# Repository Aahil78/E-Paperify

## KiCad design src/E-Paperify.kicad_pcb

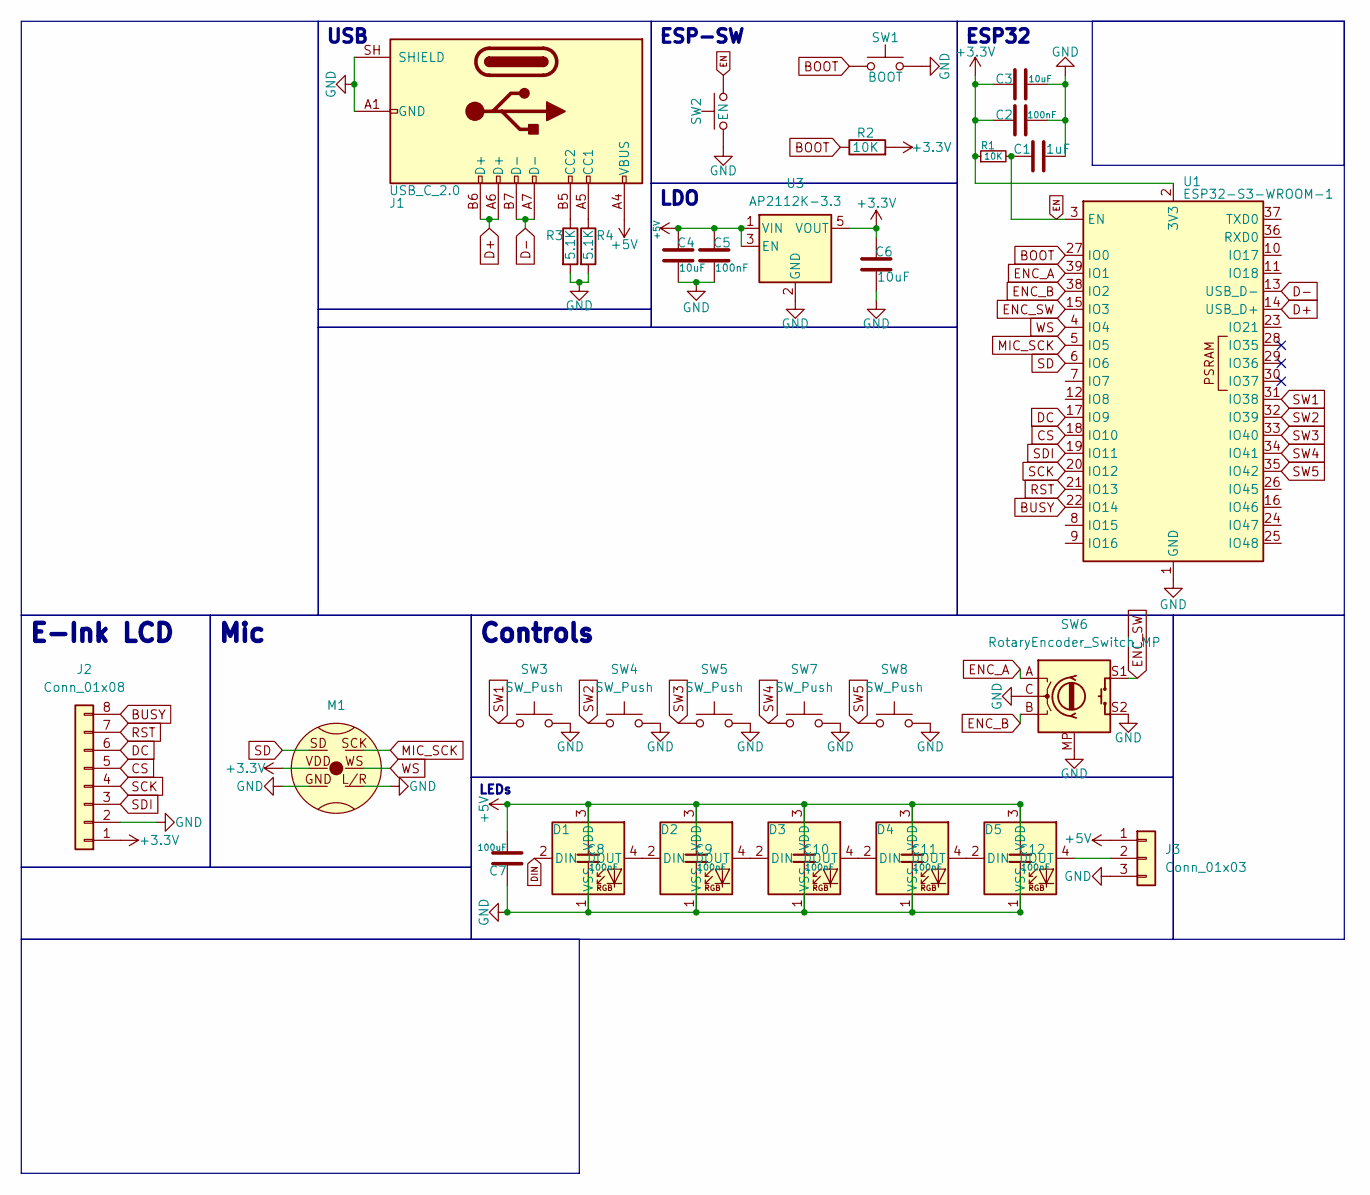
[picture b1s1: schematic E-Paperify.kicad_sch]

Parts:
C1: 1uF; C_0805_2012Metric_Pad1.18x1.45mm_HandSolder
C2, C5, C8, C9, C10, C11, C12: 100nF; C_0805_2012Metric_Pad1.18x1.45mm_HandSolder
C3, C4, C6: 10uF; C_0805_2012Metric_Pad1.18x1.45mm_HandSolder
C7: 100uF; C_0805_2012Metric_Pad1.18x1.45mm_HandSolder
D1, D2, D3, D4, D5: SK6812MINI-E; MX_SK6812MINI-E
J1: USB_C_2.0; USB_C_Receptacle_GCT_USB4110
J2: Conn_01x08; PinHeader_1x08_P2.54mm_Vertical
J3: Conn_01x03; PinHeader_1x03_P2.54mm_Vertical
M1: INMP441
R1, R2: 10K; R_0805_2012Metric_Pad1.20x1.40mm_HandSolder
R3, R4: 5.1K; R_0805_2012Metric_Pad1.20x1.40mm_HandSolder
SW1: BOOT; SW_Push_1P1T_XKB_TS-1187A
SW2: EN; SW_Push_1P1T_XKB_TS-1187A
SW3, SW4, SW5, SW7, SW8: SW_Push; SW_Hotswap_Kailh_MX_1.00u
SW6: RotaryEncoder_Switch_MP; RotaryEncoder_Alps_EC11E-Switch_Vertical_H20mm
U1: ESP32-S3-WROOM-1
U3: AP2112K-3.3; SOT-23-5

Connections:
+3.3V: C2.1, C3.1, C6.1, J2.1, M1.VDD, R1.1, R2.2, U1.2 (3V3), U3.5 (VOUT)
+5V: C4.1, C5.1, C7.2, C8.1, C9.1, C10.1, C11.1, C12.1, D1.3 (VDD), D2.3 (VDD), D3.3 (VDD), D4.3 (VDD), D5.3 (VDD), J1.A4 (VBUS), J1.A9 (VBUS), J1.B4 (VBUS), J1.B9 (VBUS), J3.1, U3.1 (VIN), U3.3 (EN)
BOOT: R2.1, SW1.1, U1.27 (IO0)
BUSY: J2.8, U1.22 (IO14)
CS: J2.5, U1.18 (IO10)
D+: J1.A6 (D+), J1.B6 (D+), U1.14 (USB_D+)
D-: J1.A7 (D-), J1.B7 (D-), U1.13 (USB_D-)
DC: J2.6, U1.17 (IO9)
DIN: D1.2 (DIN)
EN: C1.1, R1.2, SW2.2, U1.3 (EN)
ENC_A: SW6.A, U1.39 (IO1)
ENC_B: SW6.B, U1.38 (IO2)
ENC_SW: SW6.S1, U1.15 (IO3)
GND: C1.2, C2.2, C3.2, C4.2, C5.2, C6.2, C7.1, C8.2, C9.2, C10.2, C11.2, C12.2, D1.1 (VSS), D2.1 (VSS), D3.1 (VSS), D4.1 (VSS), D5.1 (VSS), J1.A1 (GND), J1.A12 (GND), J1.B1 (GND), J1.B12 (GND), J1.SH (SHIELD), J2.2, J3.3, M1.GND, M1.L/R, R3.2, R4.2, SW1.2, SW2.1, SW3.2, SW4.2, SW5.2, SW6.C, SW6.MP, SW6.S2, SW7.2, SW8.2, U1.1 (GND), U1.40 (GND), U1.41 (GND), U3.2 (GND)
MIC_SCK: M1.SCK, U1.5 (IO5)
unnamed: D1.4 (DOUT), D2.2 (DIN)
unnamed: D2.4 (DOUT), D3.2 (DIN)
unnamed: D3.4 (DOUT), D4.2 (DIN)
unnamed: D4.4 (DOUT), D5.2 (DIN)
unnamed: D5.4 (DOUT), J3.2
unnamed: J1.A5 (CC1), R4.1
unnamed: J1.B5 (CC2), R3.1
RST: J2.7, U1.21 (IO13)
SCK: J2.4, U1.20 (IO12)
SD: M1.SD, U1.6 (IO6)
SDI: J2.3, U1.19 (IO11)
SW1: SW3.1, U1.31 (IO38)
SW2: SW4.1, U1.32 (IO39)
SW3: SW5.1, U1.33 (IO40)
SW4: SW7.1, U1.34 (IO41)
SW5: SW8.1, U1.35 (IO42)
WS: M1.WS, U1.4 (IO4)

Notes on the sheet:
ESP32
LEDs
E-Ink LCD
LDO
Mic
ESP-SW
Controls
USB

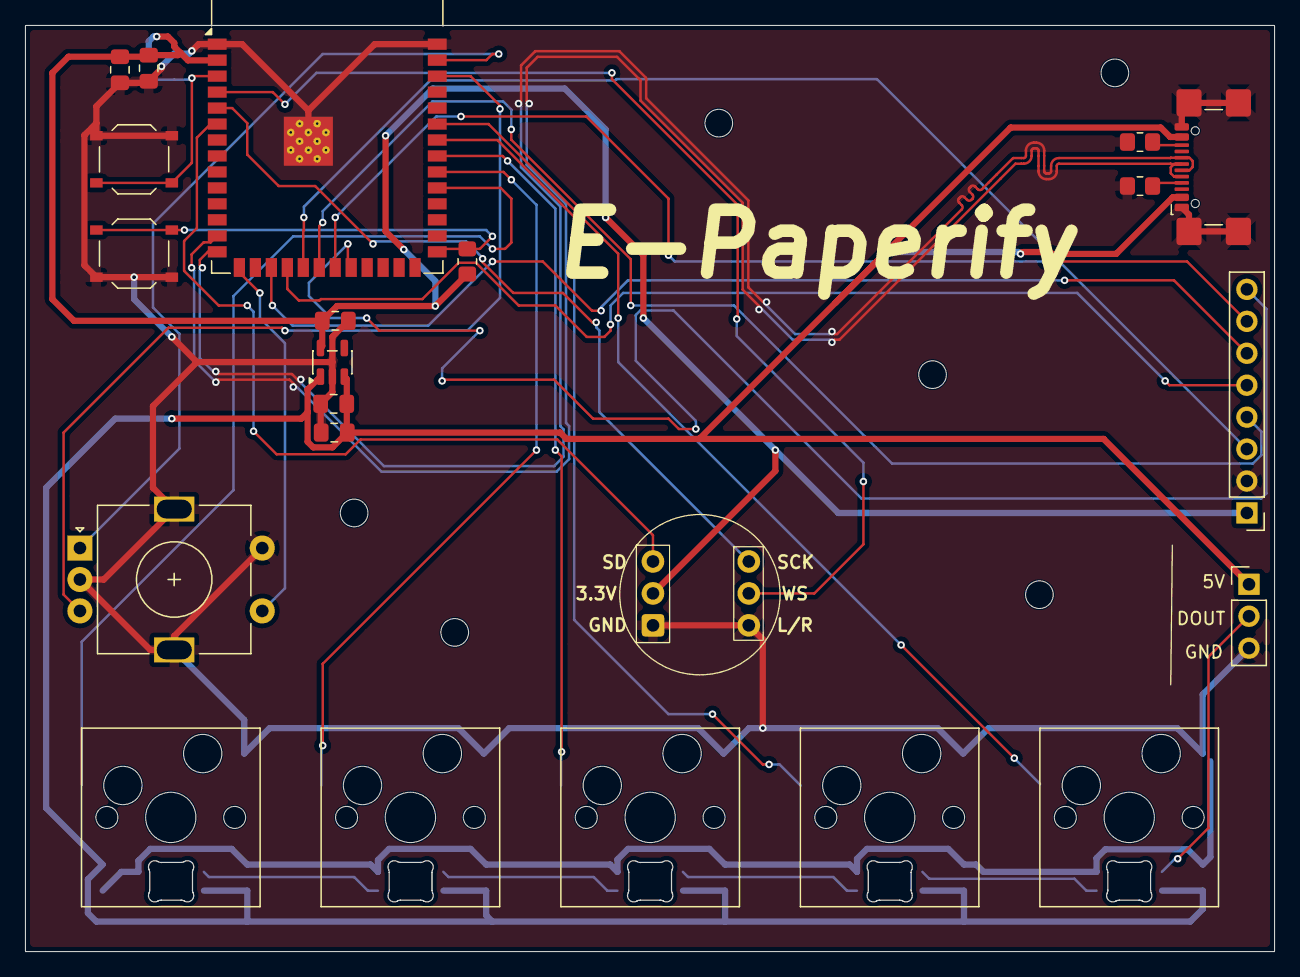
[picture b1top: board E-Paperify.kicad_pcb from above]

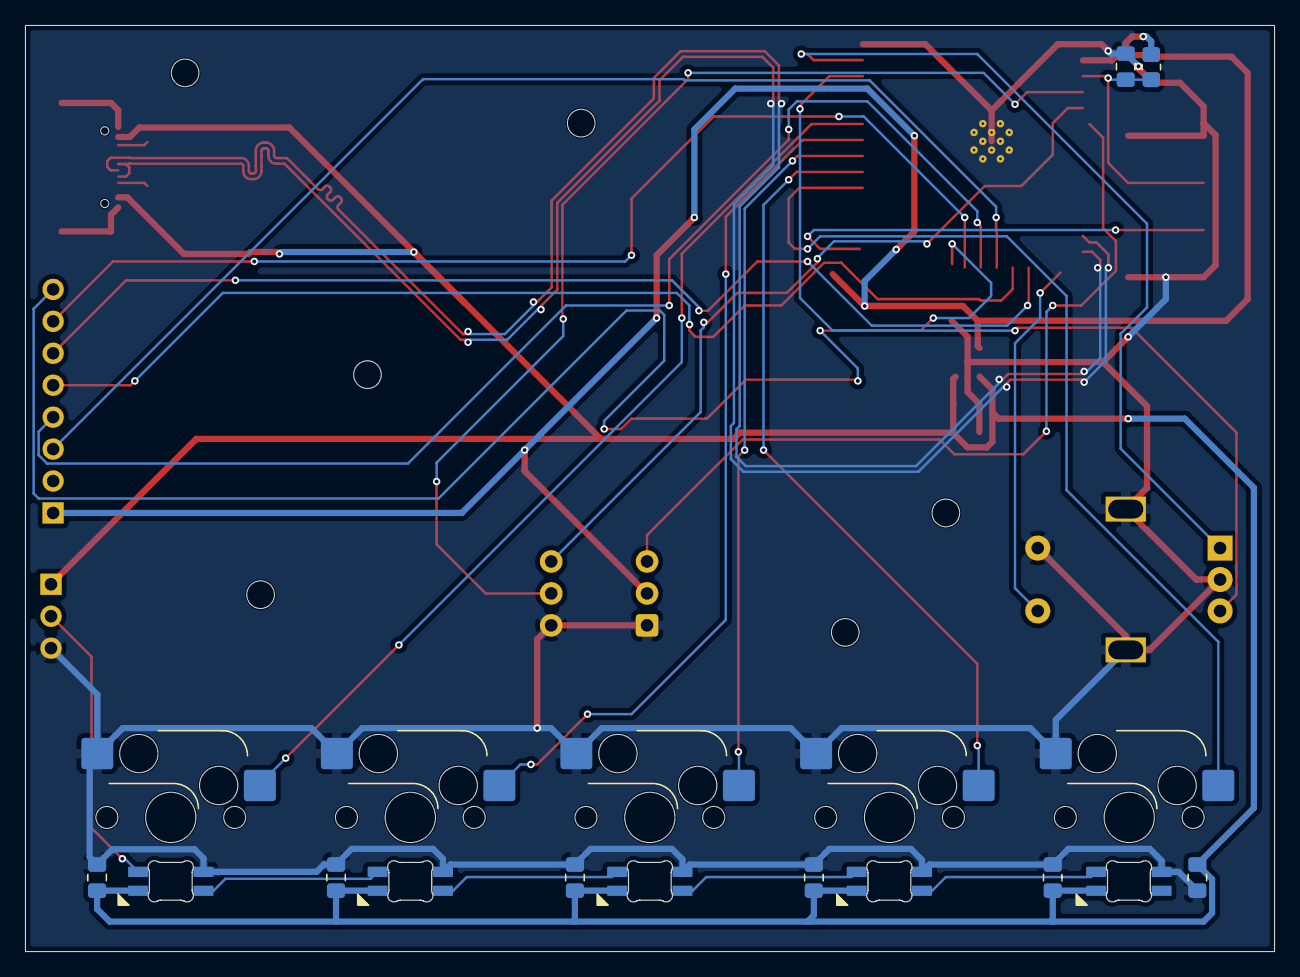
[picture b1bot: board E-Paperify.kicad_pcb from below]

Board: 2 copper layers, 99.3 x 73.7 mm, 35 parts (8 on the bottom side), 31 nets.
